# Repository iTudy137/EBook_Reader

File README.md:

### Copyright Dinca Tudor-Cristian 332CA 2025

# OpenBook E-Reader

1. [Block Diagram](#block-diagram)
2. [Bill of Materials](#bill-of-materials)
3. [Hardware Details](#hardware-functionality)
4. [ESP32-C6 Pins](#ESP32-C6-pin-mapping)

# Block Diagram

---

# Bill of Materials

| Qty | Description                                                                                                                                                                                                                                                                                                                                                                                                                                                                                          | Value                                                                          | Parts                                                                                                   | AVAILABILITY            | CHECK_PRICES                                                                                                                                                                                                                                                                                                                                                                                                                                                                                                                                                                                 | DATASHEET                                                                                                                                                |
| --- | ---------------------------------------------------------------------------------------------------------------------------------------------------------------------------------------------------------------------------------------------------------------------------------------------------------------------------------------------------------------------------------------------------------------------------------------------------------------------------------------------------- | ------------------------------------------------------------------------------ | ------------------------------------------------------------------------------------------------------- | ----------------------- | -------------------------------------------------------------------------------------------------------------------------------------------------------------------------------------------------------------------------------------------------------------------------------------------------------------------------------------------------------------------------------------------------------------------------------------------------------------------------------------------------------------------------------------------------------------------------------------------- | -------------------------------------------------------------------------------------------------------------------------------------------------------- |
| 1   | LED                                                                                                                                                                                                                                                                                                                                                                                                                                                                                                  |                                                                                | CHG_LED                                                                                                 | In Stock                | https://ro.mouser.com/ProductDetail/ams-OSRAM/LB-Q99G.01-P1R1-35-1?qs=IPgv5n7u5QZHWhEkNg3xgA%3D%3D                                                                                                                                                                                                                                                                                                                                                                                                                                                                                           | https://ro.mouser.com/datasheet/2/588/prd_pim_datasheet_23471863_EN_pdf-3317093.pdf                                                                      |
| 1   | SMD solder JUMPER                                                                                                                                                                                                                                                                                                                                                                                                                                                                                    |                                                                                | SJ1                                                                                                     | In Stock                | https://ro.mouser.com/ProductDetail/Vishay-Dale/CRCW04020000Z0EEHP?qs=sGAEpiMZZMtlubZbdhIBIKF%2FTFcY2hSpgvMg4uB1QYw%3D                                                                                                                                                                                                                                                                                                                                                                                                                                                                       | https://www.vishay.com/docs/20043/crcwhpe3.pdf                                                                                                           |
| 1   | CAPACITOR, European symbol                                                                                                                                                                                                                                                                                                                                                                                                                                                                           | 0.1uF/50V                                                                      | EPD_C5                                                                                                  | In Stock                | [https://ro.mouser.com/ProductDetail/Walsin/0402N151F500CT?qs=ZrPdAQfJ6DML0ptnM%2FXFsA%3D%3D&utm_id=6470900573&utm_source=google&utm_medium=cpc&utm_marketing_tactic=emeacorp&gad_source=1&gclid=Cj0KCQjwhr6_BhD4ARIsAH1YdjB1QLZVHFVJAtMd1vwkIhjE6qN7B49LVIzW80TzkBiTwUEhFkgf5tQaAoaREALw_wcB](https://ro.mouser.com/ProductDetail/Walsin/0402N151F500CT?qs=ZrPdAQfJ6DML0ptnM%2FXFsA%3D%3D&utm_id=6470900573&utm_source=google&utm_medium=cpc&utm_marketing_tactic=emeacorp&gad_source=1&gclid=Cj0KCQjwhr6_BhD4ARIsAH1YdjB1QLZVHFVJAtMd1vwkIhjE6qN7B49LVIzW80TzkBiTwUEhFkgf5tQaAoaREALw_wcB) | [https://ro.mouser.com/datasheet/2/210/WTC_MLCC_General_Purpose-1534899.pdf](https://ro.mouser.com/datasheet/2/210/WTC_MLCC_General_Purpose-1534899.pdf) |
| 1   | RESISTOR, European symbol                                                                                                                                                                                                                                                                                                                                                                                                                                                                            | 0.47                                                                           | R3                                                                                                      | In Stock                | https://ro.mouser.com/ProductDetail/Panasonic/ERJ-2BQJR47X?qs=18kBAoNi3c8r%252BkU3FsPM2Q%3D%3D                                                                                                                                                                                                                                                                                                                                                                                                                                                                                               | https://industrial.panasonic.com/cdbs/www-data/pdf/RDN0000/AOA0000C313.pdf                                                                               |
| 1   | RESISTOR, European symbol                                                                                                                                                                                                                                                                                                                                                                                                                                                                            | 100K                                                                           | R1_PWRUSB                                                                                               | In Stock                | [https://ro.mouser.com/ProductDetail/Welwyn-Components-TT-Electronics/WCR0402-100KFA?qs=%2F5Ar%2FAxv93DcWIrqMX6zjw%3D%3D](https://ro.mouser.com/ProductDetail/Welwyn-Components-TT-Electronics/WCR0402-100KFA?qs=%2F5Ar%2FAxv93DcWIrqMX6zjw%3D%3D)                                                                                                                                                                                                                                                                                                                                           | https://ro.mouser.com/datasheet/2/414/TTRB_S_A0012915158_1-2565570.pdf                                                                                   |
| 6   | CAPACITOR, European symbol                                                                                                                                                                                                                                                                                                                                                                                                                                                                           | 100nF                                                                          | C1, C2, C6, C8, C10, C_DELAY                                                                            | In Stock                | https://ro.mouser.com/ProductDetail/KYOCERA-AVX/04023C104KAT2A-62?qs=%252BdQmOuGyFcH%2FNuvX5KIF9Q%3D%3D                                                                                                                                                                                                                                                                                                                                                                                                                                                                                      | https://ro.mouser.com/datasheet/2/40/X7RDielectric-2943470.pdf                                                                                           |
| 2   | CAPACITOR, European symbol                                                                                                                                                                                                                                                                                                                                                                                                                                                                           | 100nF                                                                          | C4_USB, C9                                                                                              | In Stock                | https://ro.mouser.com/ProductDetail/KYOCERA-AVX/04023C104KAT2A-62?qs=%252BdQmOuGyFcH%2FNuvX5KIF9Q%3D%3D                                                                                                                                                                                                                                                                                                                                                                                                                                                                                      | https://ro.mouser.com/datasheet/2/40/X7RDielectric-2943470.pdf                                                                                           |
| 1   | POLARIZED CAPACITOR, European symbol                                                                                                                                                                                                                                                                                                                                                                                                                                                                 | 100uF TANT                                                                     | C3                                                                                                      | In Stock                | https://ro.mouser.com/ProductDetail/KYOCERA-AVX/TCJB106M020R0150E?qs=DPoM0jnrROXN%252B%252BcGKR%2FSYA%3D%3D&srsltid=AfmBOoo1FzSeu9BDfQsWfsf6aT2Nks-cpAUpOlGyrzjX172lod-o8mYB                                                                                                                                                                                                                                                                                                                                                                                                                 | https://ro.mouser.com/datasheet/2/40/TCJ-2887130.pdf                                                                                                     |
| 16  | RESISTOR, European symbol                                                                                                                                                                                                                                                                                                                                                                                                                                                                            | 10K                                                                            | R1, R1_PINH, R1_PINH1, R2-PINH, R2-PINH1, R4, R5, R6, R7, R8, R9, R10, R_BOOT, R_CHANGE, R_CL1, R_RESET | In Stock                | https://ro.mouser.com/ProductDetail/YAGEO/RC0402FR-07100KL?qs=mnq%2FyloZIXzTlUn7JAHSWg%3D%3D                                                                                                                                                                                                                                                                                                                                                                                                                                                                                                 | https://ro.mouser.com/datasheet/2/447/YAGEO_PYu_RC_Group_51_RoHS_L_12-3313492.pdf                                                                        |
| 1   | CAPACITOR, European symbol                                                                                                                                                                                                                                                                                                                                                                                                                                                                           | 10uF                                                                           | C7                                                                                                      | In Stock                | https://ro.mouser.com/ProductDetail/KYOCERA-AVX/KAM05AR71E103KH?qs=Jm2GQyTW%2FbgMbf7pmhTrvw%3D%3D                                                                                                                                                                                                                                                                                                                                                                                                                                                                                            | https://ro.mouser.com/datasheet/2/40/AutoMLCCKAM-3216307.pdf                                                                                             |
| 1   | Micro SD Card Socket, Push-Push Type, Top Mount, SMT, H=1.83mm, 10u                                                                                                                                                                                                                                                                                                                                                                                                                                  | 112A-TAAR-R03_ATTEND                                                           | J4                                                                                                      | In Stock                | https://www.soselectronic.com/ro-ro/products/attend/112a-taar-r03-116052                                                                                                                                                                                                                                                                                                                                                                                                                                                                                                                     | https://cdn.soselectronic.com/productdata/bd/ac/42954337/112a-taar-r03.pdf                                                                               |
| 1   | RESISTOR, European symbol                                                                                                                                                                                                                                                                                                                                                                                                                                                                            | 15                                                                             | R_CAPACITOR                                                                                             | In Stock                | https://ro.mouser.com/ProductDetail/Bourns/CR0402-FX-15R0GLF?qs=sGAEpiMZZMtlubZbdhIBICGkyIRIR3aIuucn1Gj71Hk%3D                                                                                                                                                                                                                                                                                                                                                                                                                                                                               | https://ro.mouser.com/datasheet/2/54/cr-1858361.pdf                                                                                                      |
| 1   | CAPACITOR, European symbol                                                                                                                                                                                                                                                                                                                                                                                                                                                                           | 1uF                                                                            | C5                                                                                                      | In Stock                | https://ro.mouser.com/ProductDetail/TAIYO-YUDEN/MAASL105CC7105MFCA01?qs=HFfMDpzxxd1Fn%2FInbJA7vw%3D%3D                                                                                                                                                                                                                                                                                                                                                                                                                                                                                       | https://ro.mouser.com/datasheet/2/396/TAIYO_YUDEN_04_27_2024_c_mlcc_A_e1-3451516.pdf                                                                     |
| 9   | CAPACITOR, European symbol                                                                                                                                                                                                                                                                                                                                                                                                                                                                           | 1uF/50V                                                                        | EPD_C1, EPD_C2, EPD_C6, EPD_C7, EPD_C8, EPD_C9, EPD_C10, EPD_C11, EPD_C12                               | In Stock                | https://ro.mouser.com/ProductDetail/TAIYO-YUDEN/MAASU32NSB7105KTCA01?qs=sGAEpiMZZMukHu%252BjC5l7YTv8iICJ6%2Fau7q9mUPeDLKU%3D                                                                                                                                                                                                                                                                                                                                                                                                                                                                 | https://ro.mouser.com/datasheet/2/396/TDK_4_24_2024_MAASU32NSB7105KTCA01_SS-3440852.pdf                                                                  |
| 1   | RESISTOR, European symbol                                                                                                                                                                                                                                                                                                                                                                                                                                                                            | 2.2                                                                            | R2                                                                                                      | In Stock                | https://ro.mouser.com/ProductDetail/YAGEO/RC0402JR-072R2L?qs=sGAEpiMZZMtlubZbdhIBIDHZZHtX2mqkbiSU5pja5tk%3D                                                                                                                                                                                                                                                                                                                                                                                                                                                                                  | https://ro.mouser.com/datasheet/2/447/YAGEO_PYu_RC_Group_51_RoHS_L_12-3313492.pdf                                                                        |
| 1   | RESISTOR, European symbol                                                                                                                                                                                                                                                                                                                                                                                                                                                                            | 200                                                                            | R1_BAT                                                                                                  | In Stock                | https://ro.mouser.com/ProductDetail/Panasonic/ERJ-U02D2000X?qs=sGAEpiMZZMtlubZbdhIBICc%2FOdEF9c%2FXmWyuMKnNE4Y%3D                                                                                                                                                                                                                                                                                                                                                                                                                                                                            | https://industrial.panasonic.com/cdbs/www-data/pdf/RDP0000/AOA0000C334.pdf                                                                               |
| 2   | P-channel MOSFETs                                                                                                                                                                                                                                                                                                                                                                                                                                                                                    | 20V/4.2A/52mO/1.4W                                                             | Q1, Q2                                                                                                  | In Stock                | https://ro.mouser.com/ProductDetail/Diodes-Incorporated/DMG2305UX-7?qs=L1DZKBg7t5F%2FNBHrjfxC%252Bg%3D%3D&utm_id=6470900573&utm_source=google&utm_medium=cpc&utm_marketing_tactic=emeacorp&gad_source=1&gclid=Cj0KCQjwhr6_BhD4ARIsAH1YdjDoeyMOZmPtNXLmjl3ngvDMqv7Q8ZoL57iNF_dxsnN5I3NCajG9PIEaAkOEEALw_wcB                                                                                                                                                                                                                                                                                   | https://www.diodes.com/assets/Datasheets/DMG2305UX.pdf                                                                                                   |
| 1   | RESISTOR, European symbol                                                                                                                                                                                                                                                                                                                                                                                                                                                                            | 2K                                                                             | R2_BAT                                                                                                  | In Stock                | https://ro.mouser.com/ProductDetail/Vishay-Dale/CRCW04022K00JNTD?qs=D1%252BtGGlbRE%252BwoJgrHBlX1g%3D%3D                                                                                                                                                                                                                                                                                                                                                                                                                                                                                     | https://www.vishay.com/docs/20008/dcrcw.pdf                                                                                                              |
| 2   | CAPACITOR, European symbol                                                                                                                                                                                                                                                                                                                                                                                                                                                                           | 4.7uF                                                                          | C1_BAT, C2_BAT                                                                                          | In Stock                | https://ro.mouser.com/ProductDetail/KEMET/C0402C475K8PACTU?qs=ulEaXIWI0c9ebKRT3r3htg%3D%3D                                                                                                                                                                                                                                                                                                                                                                                                                                                                                                   | https://ro.mouser.com/datasheet/2/447/KEM_C1006_X5R_SMD-3316465.pdf                                                                                      |
| 3   | CAPACITOR, European symbol                                                                                                                                                                                                                                                                                                                                                                                                                                                                           | 4.7uF                                                                          | C1_BAT1, C1_BAT2, C5_USB                                                                                | In Stock                | https://ro.mouser.com/ProductDetail/KEMET/C0402C475K8PACTU?qs=ulEaXIWI0c9ebKRT3r3htg%3D%3D                                                                                                                                                                                                                                                                                                                                                                                                                                                                                                   | https://ro.mouser.com/datasheet/2/447/KEM_C1006_X5R_SMD-3316465.pdf                                                                                      |
| 1   | CAPACITOR, European symbol                                                                                                                                                                                                                                                                                                                                                                                                                                                                           | 4.7uF/25V                                                                      | C4                                                                                                      | In Stock                | https://ro.mouser.com/ProductDetail/KYOCERA-AVX/CM05X5R475M25AH?qs=MyNHzdoqoQJvFdZaEuclBg%3D%3D                                                                                                                                                                                                                                                                                                                                                                                                                                                                                              | https://ro.mouser.com/datasheet/2/40/CM_Series_e-2835982.pdf                                                                                             |
| 2   | RESISTOR, European symbol                                                                                                                                                                                                                                                                                                                                                                                                                                                                            | 5k1                                                                            | R2-USB, R2-USB1                                                                                         | In Stock                | https://ro.mouser.com/ProductDetail/Vishay-Beyschlag/MCS04020C5101FE000?qs=sGAEpiMZZMvdGkrng054t4QdAY%2FQ0LweI%252Blr2dxb1tw%3D                                                                                                                                                                                                                                                                                                                                                                                                                                                              | https://www.vishay.com/docs/28705/mcx0x0xpro.pdf                                                                                                         |
| 1   |                                                                                                                                                                                                                                                                                                                                                                                                                                                                                                      | 68uH                                                                           | L1                                                                                                      | In Stock                | https://www.digikey.de/en/products/detail/w%C3%BCrth-elektronik/744043680/1638515?srsltid=AfmBOopBgKiLEiasm_81lCn1a11PPzCKGdFMi1JqFSJ8kTFummtD-o78                                                                                                                                                                                                                                                                                                                                                                                                                                           | https://www.we-online.com/components/products/datasheet/744043680.pdf                                                                                    |
| 1   | Voltage Detector with Adjustable Delay Time: CMOS processes are utilized to develop high precision, low current consumption CMOS reset ICs that allow arbitrary setting of the delay time. The extensive lineup includes both Nch Open Drain and CMOS output types in a wide range of detection voltages (from 2.3V to 6.0V, in 0.1V steps), enabling selection of the ideal solution based on customer requirements. In addition, the entire series is of course both lead-free and RoHS-compliant. | BD5229G-TR                                                                     | IC1                                                                                                     | In Stock                | https://ro.mouser.com/ProductDetail/ROHM-Semiconductor/BD5229G-1TR?qs=HoCaDK9Nz5dKF71NR7zdNw%3D%3D&utm_id=6470900573&utm_source=google&utm_medium=cpc&utm_marketing_tactic=emeacorp&gad_source=1&gclid=Cj0KCQjwhr6_BhD4ARIsAH1YdjAIpE6_2POwpfdw6DR7vakM2s_-m0lDV7xt7KL-rvPk8BHaBd_4NeAaAozdEALw_wcB                                                                                                                                                                                                                                                                                          | https://fscdn.rohm.com/en/products/databook/datasheet/ic/power/voltage_detector/bd52xxg-1-e.pdf                                                          |
| 3   |                                                                                                                                                                                                                                                                                                                                                                                                                                                                                                      | BUTTON_CUSYOMV1                                                                | BOOT_BUTTON, CHANGE_BUTTON, RESET_BUTTON                                                                | Restricted Availability | https://ro.mouser.com/ProductDetail/Panasonic/EVQ-P7B01K?qs=Ow%252BOiPmaljGz0yYR%252BWV0ZQ%3D%3D                                                                                                                                                                                                                                                                                                                                                                                                                                                                                             | https://industry.panasonic.com/global/en/downloads/?file_cd=402906&tab=catalog&series_cd=3457                                                            |
| 1   | Cap 0.011F 3.3V 1210 Flat Check availability                                                                                                                                                                                                                                                                                                                                                                                                                                                         | CPH3225A                                                                       | C10_SUPERCAP                                                                                            | Not in stock            | [https://www.snapeda.com/parts/CPH3225A/Seiko+Instruments/view-part/?ref=eda](https://www.snapeda.com/parts/CPH3225A/Seiko+Instruments/view-part/?ref=eda)                                                                                                                                                                                                                                                                                                                                                                                                                                   | https://www.snapeda.com/parts/CPH3225A/Seiko%20Instruments/datasheet/                                                                                    |
| 1   | Real Time Clock Serial 16-Pin SOIC W T/R     Check availability                                                                                                                                                                                                                                                                                                                                                                                                                                      | DS3231SN#                                                                      | U3                                                                                                      | In Stock                | [https://www.snapeda.com/parts/DS3231SN%23/Analog+Devices/view-part/?ref=eda](https://www.snapeda.com/parts/DS3231SN%23/Analog+Devices/view-part/?ref=eda)                                                                                                                                                                                                                                                                                                                                                                                                                                   | https://www.snapeda.com/parts/DS3231SN%23/Analog%20Devices/datasheet/                                                                                    |
| 1   | Check availability                                                                                                                                                                                                                                                                                                                                                                                                                                                                                   | ESP32-C6-WROOM-1-N8                                                            | U2                                                                                                      | In Stock                | [https://www.snapeda.com/parts/ESP32-C6-WROOM-1-N8/Espressif+Systems/view-part/?ref=eda](https://www.snapeda.com/parts/ESP32-C6-WROOM-1-N8/Espressif+Systems/view-part/?ref=eda)                                                                                                                                                                                                                                                                                                                                                                                                             | https://www.snapeda.com/parts/ESP32-C6-WROOM-1-N8/Espressif%20Systems/datasheet/                                                                         |
| 1   | VARISTOR                                                                                                                                                                                                                                                                                                                                                                                                                                                                                             | ESP32C6_VARISTORCN1812                                                         | PFMF.050.1                                                                                              | In Stock                | https://ro.mouser.com/ProductDetail/Schurter/PFMF.050.2?qs=1auRipcfynCums5v1iucSA%3D%3D                                                                                                                                                                                                                                                                                                                                                                                                                                                                                                      | https://ro.mouser.com/datasheet/2/358/typ_PFMF-1275918.pdf                                                                                               |
| 2   | Schottky Barrier Rectifier Diode                                                                                                                                                                                                                                                                                                                                                                                                                                                                     | ESP32_WROVER_AVX---SD0805S020S1R0_AVX_SD0805S020S1R0_0_0AVX_SD0805S020S1R0_0_0 | D2, D7                                                                                                  | In Stock                | https://ro.mouser.com/ProductDetail/KYOCERA-AVX/SD0805S020S1R0?qs=jCA%252BPfw4LHbpkAoSnwrdjw%3D%3D                                                                                                                                                                                                                                                                                                                                                                                                                                                                                           | [http://datasheets.avx.com/schottky.pdf](http://datasheets.avx.com/schottky.pdf)                                                                         |
| 1   | Integrated Environmental Unit                                                                                                                                                                                                                                                                                                                                                                                                                                                                        | ESP32_WROVER_BME680_BME680                                                     | SENSOR2                                                                                                 | In Stock                | https://ro.mouser.com/ProductDetail/Bosch-Sensortec/BME680?qs=v271MhAjFHjo0yA%2FC4OnDQ%3D%3D                                                                                                                                                                                                                                                                                                                                                                                                                                                                                                 | [https://ro.mouser.com/datasheet/2/783/BST_BME680_DS001-1509608.pdf](https://ro.mouser.com/datasheet/2/783/BST_BME680_DS001-1509608.pdf)                 |
| 1   | MCP73831T Li-Ion, Li-Pol Controller                                                                                                                                                                                                                                                                                                                                                                                                                                                                  | ESP32_WROVER_SPARKFUN-IC-POWER_MCP73831                                        | MCP73831                                                                                                | In Stock                | https://ro.mouser.com/ProductDetail/Microchip-Technology/MCP73831T-2DCI-OT?qs=yUQqVecv4qu38ml9qkvsJw%3D%3D                                                                                                                                                                                                                                                                                                                                                                                                                                                                                   | https://ro.mouser.com/datasheet/2/268/MCP73831_Family_Data_Sheet_DS20001984H-3441711.pdf                                                                 |
| 1   |  (0.50mm) Surface Mount, Right Angle                                                                                                                                                                                                                                                                                                                                                                                                                                                                 | FH34SRJ-24S-0.5SH_99_                                                          | J1                                                                                                      | In Stock                | https://ro.mouser.com/ProductDetail/Hirose-Connector/FH34SRJ-24S-0.5SH99?qs=vcbW%252B4%252BSTIpKBl5ap9J8Fw%3D%3D                                                                                                                                                                                                                                                                                                                                                                                                                                                                             | https://ro.mouser.com/datasheet/2/185/FH34SRJ_24S_0_5SH_99__CL0580_1255_6_99_2DDrawing_0-1615044.pdf                                                     |
| 1   | Check availability                                                                                                                                                                                                                                                                                                                                                                                                                                                                                   | MAX17048G+T10                                                                  | U4                                                                                                      | In Stock                | [https://www.snapeda.com/parts/MAX17048G+T10/Analog+Devices/view-part/?ref=eda](https://www.snapeda.com/parts/MAX17048G+T10/Analog+Devices/view-part/?ref=eda)                                                                                                                                                                                                                                                                                                                                                                                                                               | https://www.snapeda.com/parts/MAX17048G+T10/Analog%20Devices/datasheet/                                                                                  |
| 3   | ON SEMICONDUCTOR - MBR0530 - DIODE, SCHOTTKY, 0.5A, 30V, SOD-123                                                                                                                                                                                                                                                                                                                                                                                                                                     | MBR0530                                                                        | D3, D4, D5                                                                                              | In Stock                | [https://www.snapeda.com/parts/MBR0530/Onsemi/view-part/?ref=eda](https://www.snapeda.com/parts/MBR0530/Onsemi/view-part/?ref=eda)                                                                                                                                                                                                                                                                                                                                                                                                                                                           | https://www.snapeda.com/parts/MBR0530/ON%20Semiconductor/datasheet/                                                                                      |
| 6   | Check availability                                                                                                                                                                                                                                                                                                                                                                                                                                                                                   | PGB1010603MR                                                                   | D6, D8, D9, D10, D11, D12                                                                               | In Stock                | [https://www.snapeda.com/parts/PGB1010603MR/Littelfuse/view-part/?ref=eda](https://www.snapeda.com/parts/PGB1010603MR/Littelfuse/view-part/?ref=eda)                                                                                                                                                                                                                                                                                                                                                                                                                                         | https://www.snapeda.com/parts/PGB1010603MR/Littelfuse%20Inc./datasheet/                                                                                  |
| 1   | SparkFun I2C Standard Qwiic Connector                                                                                                                                                                                                                                                                                                                                                                                                                                                                | QWIIC_RIGHT_ANGLE                                                              | J3                                                                                                      | In Stock                | https://ro.mouser.com/ProductDetail/SparkFun/PRT-14417?qs=wd5RIQLrsJhgdz%2FpmZ%2F3GQ%3D%3D                                                                                                                                                                                                                                                                                                                                                                                                                                                                                                   | https://ro.mouser.com/datasheet/2/813/Qwiic_Connector_Datasheet-1223982.pdf                                                                              |
| 1   | CONN USB 2.0 TYPE-C R/A SMT                                                                                                                                                                                                                                                                                                                                                                                                                                                                          | SAMACSYS_PARTS_USB4110-GF-A                                                    | J2                                                                                                      | In Stock                | https://ro.mouser.com/ProductDetail/GCT/USB4110-GF-A?qs=KUoIvG%2F9IlYiZvIXQjyJeA%3D%3D                                                                                                                                                                                                                                                                                                                                                                                                                                                                                                       | https://ro.mouser.com/datasheet/2/837/GCT_USB4110_Product_Drawing___20k_cycles-3455479.pdf                                                               |
| 1   | MOSFET N-Ch 30V 1.5A TrenchFET SC70 Vishay Si1308EDL-T1-GE3 N-channel MOSFET Transistor, 1.5 A, 30 V, 3-Pin SC-70                                                                                                                                                                                                                                                                                                                                                                                    | SI1308EDL-T1-GE3                                                               | Q3                                                                                                      | In Stock                | [https://www.snapeda.com/parts/SI1308EDL-T1-GE3/Vishay+Siliconix/view-part/?ref=eda](https://www.snapeda.com/parts/SI1308EDL-T1-GE3/Vishay+Siliconix/view-part/?ref=eda)                                                                                                                                                                                                                                                                                                                                                                                                                     | https://www.snapeda.com/parts/SI1308EDL-T1-GE3/Vishay%20Siliconix/datasheet/                                                                             |
| 17  | Test pad                                                                                                                                                                                                                                                                                                                                                                                                                                                                                             | TPTP20R                                                                        | TP1, TP2, TP3, TP4, TP5, TP6, TP7, TP8, TP9, TP10, TP11, TP12, TP13, TP14, TP15, TP16, TP17             |                         | Custom                                                                                                                                                                                                                                                                                                                                                                                                                                                                                                                                                                                       | Custom                                                                                                                                                   |
| 1   | Low Cap. ESD Protection Auto SOT-23-6 STMicroelectronics USBLC6-2SC6Y, Dual Uni-Directional TVS Diode Array, 6-Pin SOT-23                                                                                                                                                                                                                                                                                                                                                                            | USBLC6-2SC6Y                                                                   | D1                                                                                                      | In Stock                | [https://www.snapeda.com/parts/USBLC6-2SC6Y/STMicroelectronics/view-part/?ref=eda](https://www.snapeda.com/parts/USBLC6-2SC6Y/STMicroelectronics/view-part/?ref=eda)                                                                                                                                                                                                                                                                                                                                                                                                                         | https://www.snapeda.com/parts/USBLC6-2SC6Y/STMicroelectronics/datasheet/                                                                                 |
| 1   | Check availability                                                                                                                                                                                                                                                                                                                                                                                                                                                                                   | W25Q512JVEIQ                                                                   | U1                                                                                                      | In Stock                | [https://www.snapeda.com/parts/W25Q512JVEIQ/Winbond+Electronics/view-part/?ref=eda](https://www.snapeda.com/parts/W25Q512JVEIQ/Winbond+Electronics/view-part/?ref=eda)                                                                                                                                                                                                                                                                                                                                                                                                                       | https://www.snapeda.com/parts/W25Q512JVEIQ/Winbond%20Electronics/datasheet/                                                                              |
| 1   | LDO Voltage Regulators                                                                                                                                                                                                                                                                                                                                                                                                                                                                               | XC6220A331MR-G                                                                 | IC4                                                                                                     | In Stock                | https://ro.mouser.com/ProductDetail/Torex-Semiconductor/XC6220A331MR-G?qs=AsjdqWjXhJ8ZSWznL1J0gg%3D%3D                                                                                                                                                                                                                                                                                                                                                                                                                                                                                       | https://ro.mouser.com/datasheet/2/760/xc6220-3371556.pdf                                                                                                 |

---

# Hardware Functionality

### Microcontroller - ESP32-C6
- **Interfaces:** SPI, I2C, GPIO, USB, PWM
- **Functions:** Wi-Fi/BLE communication, display control, sensor reading, user interface, power management
- **Operating Voltage:** 3.3V

### 1. E-Paper Display (Waveshare WSH-13187 7.5" / SPI)
- **Resolution:** 800x480
- **Interface:** SPI + GPIO  
  - **CS, DC, RST, BUSY**
- **Connected via dedicated header**

### 2. BME688 Sensor (Bosch)
- **Measures:** temperature, pressure, humidity, air quality
- **Interface:** I2C
- **Address:** configurable (default 0x76)
- **Operating Voltage:** 3.3V

### 3. RTC - DS3231SN
- **Function:** Real-Time Clock with supercapacitor backup
- **Interface:** I2C
- **Backup:** 1F Supercapacitor
- **Accuracy:** ±2ppm

### 4. Power Supply
- **Battery:** 2500mAh Li-Po
- **Charging IC:** MCP73831 (linear charger, 3.7V battery)
- **LDO Regulator:** 3.3V (AMS1117 or equivalent)
- **Connector:** USB-C (with ESD protection)

### 5. Battery Management
- **Fuel Gauge:** MAX17048
- **I2C, enables battery level monitoring**

### 6. SD Card
- **Interface:** SPI
- **Usage:** e-book storage

### 7. User Interface
- **RESET Button**
- **3 Input Buttons connected to GPIO + RC debouncing**
- **Functions:** menu navigation, page switching, simple interactions

### 8. Qwiic / Stemma QT Connector
- **Allows easy expansion with external I2C sensors**

---

## 🔋 Battery & Power Usage Summary

### 📦 Battery Capacity
- **2500mAh @ 3.7V = 9.25Wh**

---

### ⚡ Power Consumption Overview

| Mode                | Current Draw | Power (W) | Battery Life       |
|---------------------|--------------|-----------|---------------------|
| 🔘 Idle (Deep Sleep) | ~0.05 mA     | ~0.0002 W | ~5.7 years          |
| 😴 Light Sleep       | ~1.2 mA      | ~0.0044 W | ~86 days            |
| 📖 Active Reading    | ~77 mA       | ~0.285 W  | ~32 hours           |
| 🌐 Wi-Fi Active      | ~177 mA      | ~0.655 W  | ~14 hours           |

---

# ESP32-C6 Pin Mapping

| **ESP32-C6 Pin** | **Net Label**  | **Function**       | **Connected Component**      | **Purpose / Description**                                                                 |
|------------------|----------------|--------------------|-------------------------------|-------------------------------------------------------------------------------------------|
| EN               | RESET          | Enable             | ESP32-C6                      | Main reset input to the microcontroller                                                   |
| IO0              | INT_RTC        | GPIO (Interrupt)   | RTC DS3231SN                  | Receives interrupt signal from RTC (e.g. alarm trigger)                                  |
| IO1              | 32KHZ          | GPIO (Clock In)    | RTC DS3231SN                  | 32kHz clock output from RTC                                                               |
| IO2              | MISO           | SPI MISO           | SD Card                       | Receives data from SD card                                                                |
| IO3              | EPD_BUSY       | GPIO (Input)       | E-Paper Display               | Indicates when the E-Paper display is busy                                               |
| IO4              | SS_SD          | SPI CS             | SD Card                       | Chip select for SD card                                                                   |
| IO5              | EPD_CS         | SPI CS             | E-Paper Display               | Chip select for E-Paper display                                                           |
| IO6              | SCK            | SPI Clock          | E-Paper Display, SD Card      | Clock signal for shared SPI bus                                                           |
| IO7              | MOSI           | SPI MOSI           | E-Paper Display, SD Card      | Sends data to display and SD card                                                         |
| IO8              | GPIO9          | GPIO               | General Purpose               | Spare GPIO or future expansion                                                            |
| IO9              | IO/BOOT        | GPIO / Boot        | Boot Button                   | Used for flashing the ESP32 (held LOW on boot to enter flash mode)                       |
| IO10             | EPD_CS         | SPI CS             | E-Paper Display               | Redundant label for CS (appears twice in schematic)                                       |
| IO11             | FLASH_CS       | SPI CS             | External NOR Flash            | Chip select for SPI flash                                                                 |
| IO12             | USB_D-         | USB D-             | USB-C Connector               | Native USB communication                                                                 |
| IO13             | USB_D+         | USB D+             | USB-C Connector               | Native USB communication                                                                 |
| IO15             | IO/CHANGE      | GPIO               | General Purpose / Input       | Connected to a user-defined I/O (possibly an interrupt line or button)                   |
| IO16             | TX             | UART TX            | Serial Communication          | Transmit line for UART debugging                                                          |
| IO17             | RX             | UART RX            | Serial Communication          | Receive line for UART debugging                                                           |
| IO18             | RTC_RST        | GPIO               | RTC DS3231SN                  | Allows resetting the RTC externally                                                       |
| IO19             | I2C_PW         | GPIO (Power Ctrl)  | I2C Peripherals               | Enables power to I2C devices (BME688, MAX17048, etc.)                                     |
| IO20             | EPD_3V3_C      | GPIO (Power Ctrl)  | E-Paper Display               | Powers the EPD circuit via transistor / switch                                            |
| IO21             | SDA            | I2C Data           | BME688, RTC, MAX17048         | Shared data line for I2C peripherals                                                      |
| IO22             | SCL            | I2C Clock          | BME688, RTC, MAX17048         | Shared clock line for I2C peripherals                                                     |
| IO23             | EPD_RSR        | GPIO               | E-Paper Display               | Reset line for E-Paper display                                                            |
| 3V3              | 3V3            | Power              | All Components                | Main power rail (3.3V)                                                                    |
| GND              | GND            | Ground             | All Components                | Ground reference for the entire system                                                    |

---

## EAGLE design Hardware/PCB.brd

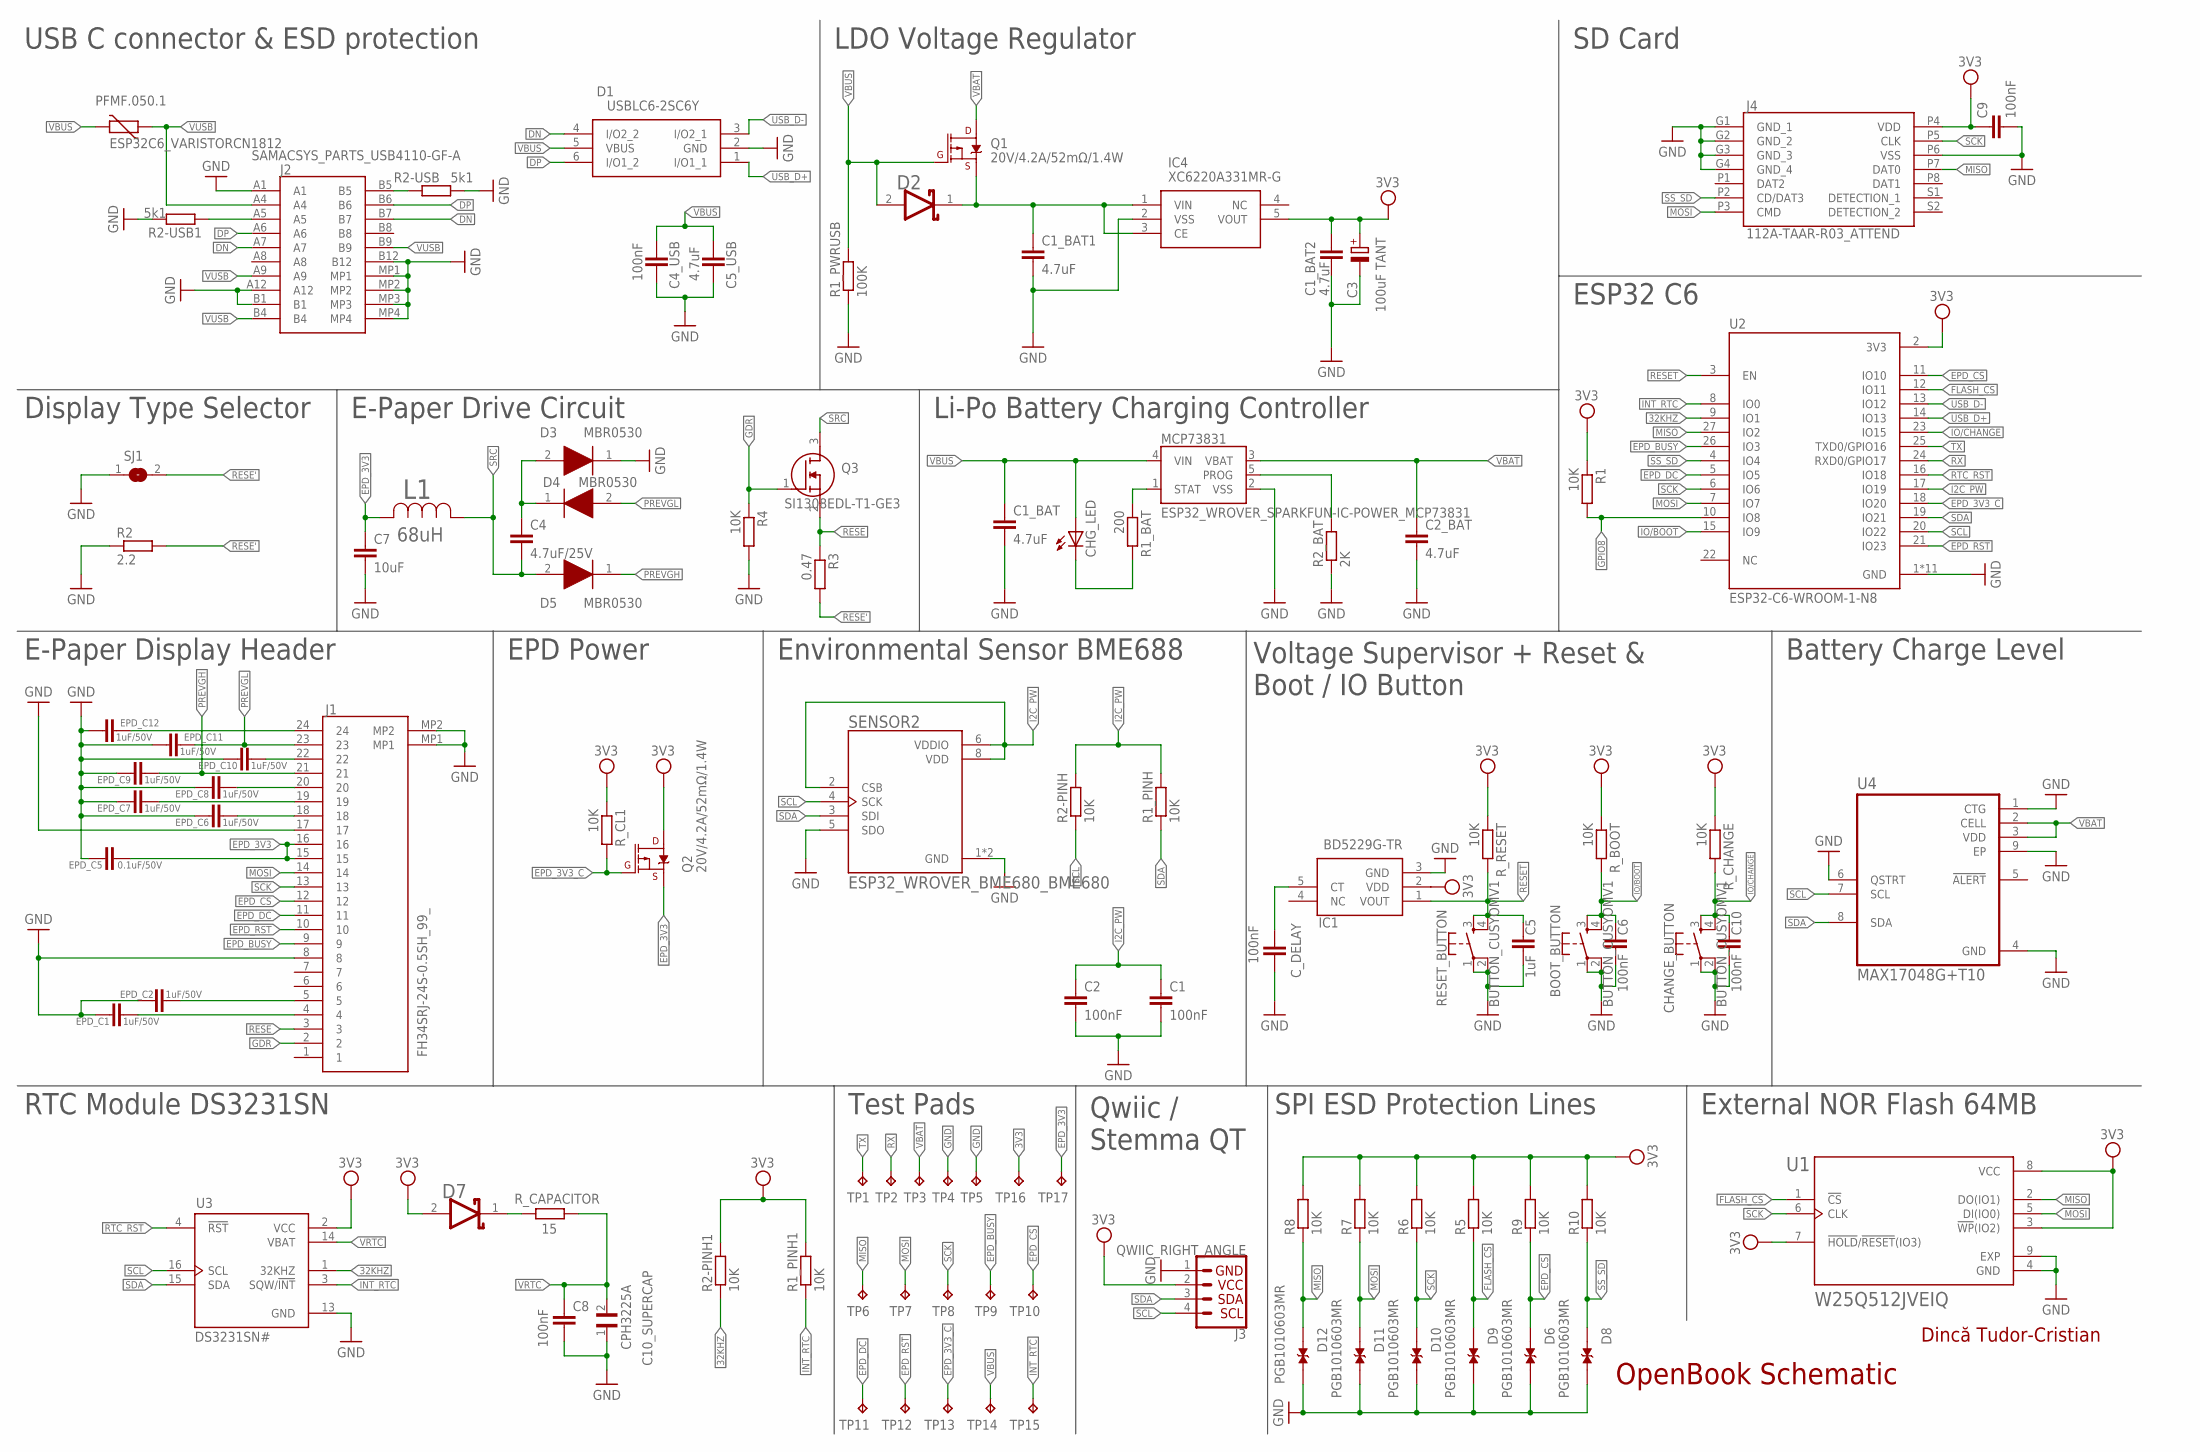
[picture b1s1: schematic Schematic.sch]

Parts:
BOOT_BUTTON: BUTTON_CUSYOMV1; MYBUTTON
C1, C2, C4_USB, C6, C8, C9, C10: 100nF; EAGLE-LTSPICE_C0402
C1_BAT, C1_BAT1, C1_BAT2, C2_BAT, C5_USB: 4.7uF; EAGLE-LTSPICE_C0402
C3: 100uF TANT; RCL_CT3528
C4: 4.7uF/25V; EAGLE-LTSPICE_C0402
C5: 1uF; EAGLE-LTSPICE_C0402
C7: 10uF; EAGLE-LTSPICE_C0402
C10_SUPERCAP: CPH3225A; CAPCP3225X100N
CHANGE_BUTTON: BUTTON_CUSYOMV1; MYBUTTON
CHG_LED: ADAFRUIT_LEDCHIP-LED0603; ADAFRUIT_CHIP-LED0603
C_DELAY: 100nF; EAGLE-LTSPICE_C0402
D1: USBLC6-2SC6Y; SOT95P280X145-6N
D2, D7: ESP32_WROVER_AVX---SD0805S020S1R0_AVX_SD0805S020S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; ESP32_WROVER_AVX---SD0805S020S1R0_AVX_SD0805S020S1R0_0
D3, D4, D5: MBR0530; SOD3716X135N
D6, D8, D9, D10, D11, D12: PGB1010603MR; DIOC1608X36N
EPD_C1, EPD_C2, EPD_C6, EPD_C7, EPD_C8, EPD_C9, EPD_C10, EPD_C11, EPD_C12: 1uF/50V; EAGLE-LTSPICE_C0402
EPD_C5: 0.1uF/50V; EAGLE-LTSPICE_C0402
IC1: BD5229G-TR; SOT95P280X125-5N
IC4: XC6220A331MR-G; SOT95P280X120-5N
J1: FH34SRJ-24S-0.5SH_99_; FH34SRJ24S05SH99
J2: SAMACSYS_PARTS_USB4110-GF-A; SAMACSYS_PARTS_USB4110GFA
J3: QWIIC_RIGHT_ANGLE; JST04_1MM_RA
J4: 112A-TAAR-R03_ATTEND; 112ATAARR03ATTEND
L1: 68uH; IND_4828-WE-TPC_WRE
MCP73831: ESP32_WROVER_SPARKFUN-IC-POWER_MCP73831; ESP32_WROVER_SPARKFUN-IC-POWER_SOT23-5
PFMF.050.1: ESP32C6_VARISTORCN1812; ESP32C6_VARISTOR_CT/CN1812
Q1, Q2: 20V/4.2A/52mΩ/1.4W; ESP32_WROVER_SPARKFUN-DISCRETESEMI_SOT23-3
Q3: SI1308EDL-T1-GE3; SOT65P210X110-3N
R1, R1_PINH, R1_PINH1, R2-PINH, R2-PINH1, R4, R5, R6, R7, R8, R9, R10: 10K; ESP32_WROVER_EAGLE-LTSPICE_R0402
R1_BAT: 200; ESP32_WROVER_EAGLE-LTSPICE_R0402
R1_PWRUSB: 100K; ESP32_WROVER_EAGLE-LTSPICE_R0402
R2: 2.2; ESP32_WROVER_EAGLE-LTSPICE_R0402
R2-USB, R2-USB1: 5k1; ESP32_WROVER_EAGLE-LTSPICE_R0402
R2_BAT: 2K; ESP32_WROVER_EAGLE-LTSPICE_R0402
R3: 0.47; ESP32_WROVER_EAGLE-LTSPICE_R0402
RESET_BUTTON: BUTTON_CUSYOMV1; MYBUTTON
R_BOOT: 10K; ESP32_WROVER_EAGLE-LTSPICE_R0402
R_CAPACITOR: 15; ESP32_WROVER_EAGLE-LTSPICE_R0402
R_CHANGE: 10K; ESP32_WROVER_EAGLE-LTSPICE_R0402
R_CL1: 10K; ESP32_WROVER_EAGLE-LTSPICE_R0402
R_RESET: 10K; ESP32_WROVER_EAGLE-LTSPICE_R0402
SENSOR2: ESP32_WROVER_BME680_BME680; ESP32_WROVER_BME680_PSON80P300X300X100-8N
SJ1: SJ
TP1, TP2, TP3, TP4, TP5, TP6, TP7, TP8, TP9, TP10, TP11, TP12, TP13, TP14, TP15, TP16, TP17: TPTP20R; TP20R
U1: W25Q512JVEIQ; SON127P600X800X80-9N
U2: ESP32-C6-WROOM-1-N8; XCVR_ESP32-C6-WROOM-1-N8
U3: DS3231SN#; SOIC127P1032X265-16N
U4: MAX17048G+T10; SON50P200X200X80-9N

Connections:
3V3: C1_BAT2.1, C3.+, C9.1, D7.2 (ANODE), IC1.2 (VDD), IC4.5 (VOUT), J3.2, J4.P4 (VDD), Q2.3 (D), R1.1, R1_PINH1.2, R2-PINH1.2, R5.2, R6.2, R7.2, R8.2, R9.2, R10.2, R_BOOT.1, R_CHANGE.1, R_CL1.1, R_RESET.1, TP16.TP, U1.3 (!WP!(IO2)), U1.7 (!HOLD!/!RESET!(IO3)), U1.8 (VCC), U2.2 (3V3), U3.2 (VCC)
32KHZ: R2-PINH1.1, U2.9 (IO1), U3.1 (32KHZ)
DN: D1.4 (I/O2_2), J2.A7, J2.B7
DP: D1.6 (I/O1_2), J2.A6, J2.B6
EPD_3V3: C7.1, EPD_C5.1, J1.15, J1.16, L1.2, Q2.2 (S), TP17.TP
EPD_3V3_C: Q2.1 (G), R_CL1.2, TP13.TP, U2.18 (IO20)
EPD_BUSY: J1.9, TP9.TP, U2.26 (IO3)
EPD_CS: D6.1, J1.12, R9.1, TP10.TP, U2.11 (IO10)
EPD_DC: J1.11, TP11.TP, U2.5 (IO5)
EPD_RST: J1.10, TP12.TP, U2.21 (IO23)
FLASH_CS: D9.1, R5.1, U1.1 (!CS), U2.12 (IO11)
GDR: J1.2, Q3.1 (G), R4.1
GND: BOOT_BUTTON.1, BOOT_BUTTON.2, C1.2, C1_BAT.2, C1_BAT1.2, C1_BAT2.2, C2.2, C2_BAT.2, C3.-, C4_USB.2, C5.2, C5_USB.2, C6.2, C7.2, C8.2, C9.2, C10.2, C10_SUPERCAP.1, CHANGE_BUTTON.1, CHANGE_BUTTON.2, C_DELAY.2, D1.2 (GND), D3.1 (K), D6.2, D8.2, D9.2, D10.2, D11.2, D12.2, EPD_C1.2, EPD_C2.2, EPD_C5.2, EPD_C6.2, EPD_C7.2, EPD_C8.2, EPD_C9.2, EPD_C10.2, EPD_C11.2, EPD_C12.2, IC1.3 (GND), IC4.2 (VSS), J1.8, J1.17, J1.MP1, J1.MP2, J2.A1, J2.A12, J2.B1, J2.B12, J2.MP1, J2.MP2, J2.MP3, J2.MP4, J3.1, J4.G1 (GND_1), J4.G2 (GND_2), J4.G3 (GND_3), J4.G4 (GND_4), J4.P6 (VSS), MCP73831.2 (VSS), R1_PWRUSB.1, R2.1, R2-USB.2, R2-USB1.2, R2_BAT.1, R4.2, RESET_BUTTON.1, RESET_BUTTON.2, SENSOR2.1 (GND), SENSOR2.5 (SDO), SENSOR2.7 (GND), SJ1.1, TP4.TP, TP5.TP, U1.4 (GND), U1.9 (EXP), U2.1 (GND), U2.28 (GND), U2.29_1 (GND), U2.29_2 (GND), U2.29_3 (GND), U2.29_4 (GND), U2.29_5 (GND), U2.29_6 (GND), U2.29_7 (GND), U2.29_8 (GND), U2.29_9 (GND), U3.13 (GND), U4.1 (CTG), U4.4 (GND), U4.6 (QSTRT), U4.9 (EP)
GPIO8: R1.2, U2.10 (IO8)
I2C_PW: C1.1, C2.1, R1_PINH.2, R2-PINH.2, SENSOR2.2 (CSB), SENSOR2.6 (VDDIO), SENSOR2.8 (VDD), U2.17 (IO19)
INT_RTC: R1_PINH1.1, TP15.TP, U2.8 (IO0), U3.3 (SQW/!INT)
IO/BOOT: BOOT_BUTTON.3, BOOT_BUTTON.4, C6.1, R_BOOT.2, U2.15 (IO9)
IO/CHANGE: C10.1, CHANGE_BUTTON.3, CHANGE_BUTTON.4, R_CHANGE.2, U2.23 (IO15)
MISO: D12.1, J4.P7 (DAT0), R8.1, TP6.TP, U1.2 (DO(IO1)), U2.27 (IO2)
MOSI: D11.1, J1.14, J4.P3 (CMD), R7.1, TP7.TP, U1.5 (DI(IO0)), U2.7 (IO7)
unnamed: J2.B5, R2-USB.1
unnamed: C1_BAT1.1, D2.1 (CATHODE), IC4.1 (VIN), IC4.3 (CE), Q1.2 (S)
unnamed: MCP73831.1 (STAT), R1_BAT.1
unnamed: CHG_LED.C, R1_BAT.2
unnamed: J2.A5, R2-USB1.1
unnamed: MCP73831.5 (PROG), R2_BAT.2
unnamed: C4.1, D3.2 (A), D4.1 (K)
unnamed: C_DELAY.1, IC1.5 (CT)
unnamed: EPD_C2.1, J1.5
unnamed: EPD_C1.1, J1.4
unnamed: D7.1 (CATHODE), R_CAPACITOR.2
unnamed: EPD_C12.1, J1.24
unnamed: EPD_C10.1, J1.22
unnamed: EPD_C8.1, J1.20
unnamed: EPD_C7.1, J1.19
unnamed: EPD_C6.1, J1.18
PREVGH: D5.1 (K), EPD_C9.1, J1.21
PREVGL: D4.2 (A), EPD_C11.1, J1.23
RESE: J1.3, Q3.2 (S), R3.1
RESE': R2.2, R3.2, SJ1.2
RESET: C5.1, IC1.1 (VOUT), RESET_BUTTON.3, RESET_BUTTON.4, R_RESET.2, U2.3 (EN)
RTC_RST: U2.16 (IO18), U3.4 (!RST)
RX: TP2.TP, U2.24 (RXD0/GPIO17)
SCK: D10.1, J1.13, J4.P5 (CLK), R6.1, TP8.TP, U1.6 (CLK), U2.6 (IO6)
SCL: J3.4, R2-PINH.1, SENSOR2.4 (SCK), U2.20 (IO22), U3.16 (SCL), U4.7 (SCL)
SDA: J3.3, R1_PINH.1, SENSOR2.3 (SDI), U2.19 (IO21), U3.15 (SDA), U4.8 (SDA)
SRC: C4.2, D5.2 (A), L1.1, Q3.3 (D)
SS_SD: D8.1, J4.P2 (CD/DAT3), R10.1, U2.4 (IO4)
TX: TP1.TP, U2.25 (TXD0/GPIO16)
USB_D+: D1.1 (I/O1_1), U2.14 (IO13)
USB_D-: D1.3 (I/O2_1), U2.13 (IO12)
VBAT: C2_BAT.1, MCP73831.3 (VBAT), Q1.3 (D), TP3.TP, U4.2 (CELL), U4.3 (VDD)
VBUS: C1_BAT.1, C4_USB.1, C5_USB.1, CHG_LED.A, D1.5 (VBUS), D2.2 (ANODE), MCP73831.4 (VIN), PFMF.050.1.2, Q1.1 (G), R1_PWRUSB.2, TP14.TP
VRTC: C8.1, C10_SUPERCAP.2, R_CAPACITOR.1, U3.14 (VBAT)
VUSB: J2.A4, J2.A9, J2.B4, J2.B9, PFMF.050.1.1

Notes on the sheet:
USB C connector & ESD protection
LDO Voltage Regulator
SD Card
ESP32 C6
Display Type Selector
E-Paper Drive Circuit
Li-Po Battery Charging Controller
E-Paper Display Header
EPD Power
Environmental Sensor BME688
Voltage Supervisor + Reset & Boot / IO Button
Battery Charge Level
RTC Module DS3231SN
Test Pads
Qwiic / Stemma QT
SPI ESD Protection Lines
External NOR Flash 64MB
OpenBook Schematic
Dincă Tudor-Cristian

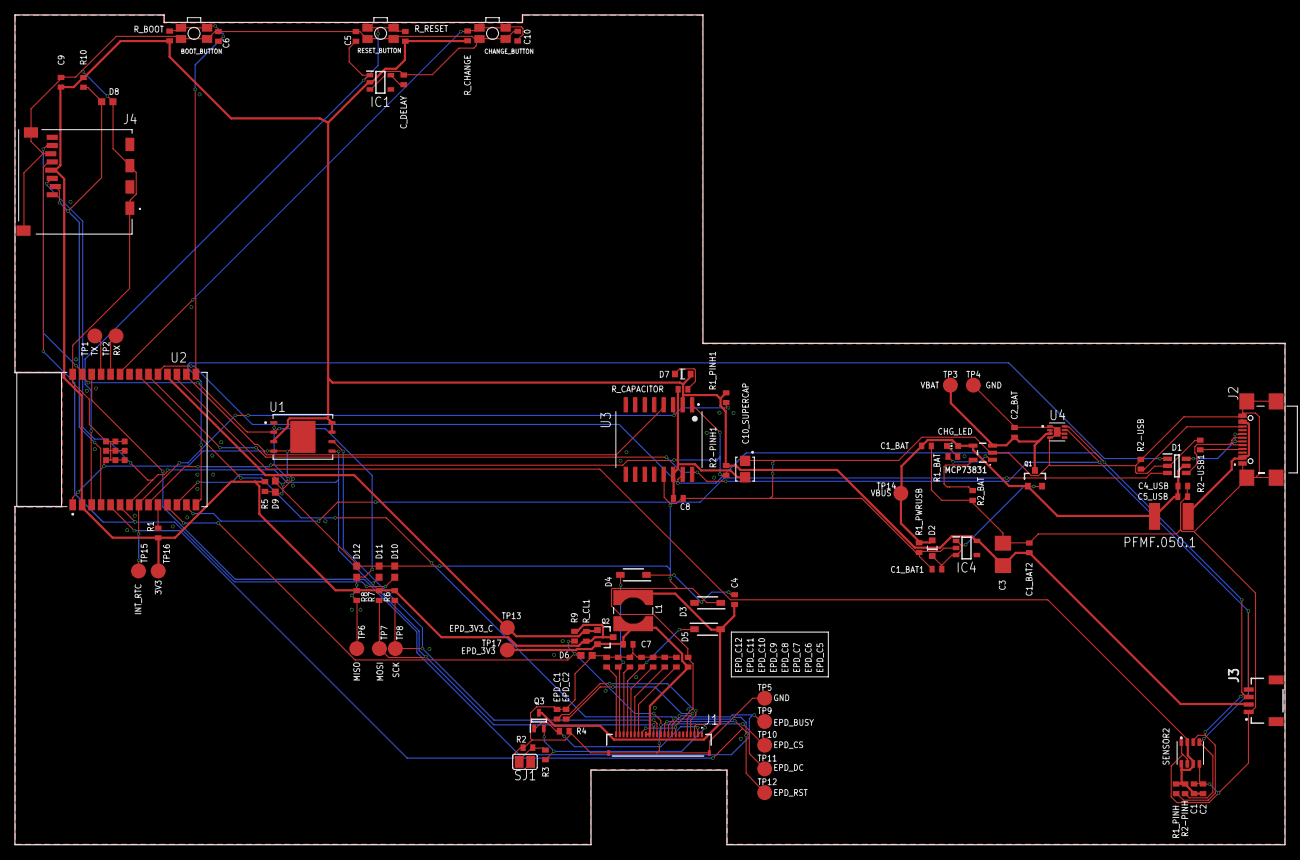
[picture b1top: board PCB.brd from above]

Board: 2 copper layers, 170.2 x 111.2 mm, 103 parts (0 on the bottom side), 55 nets.

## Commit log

2025-03-17 Created README.md
2025-04-04 Create LICENSE
2025-04-06 Added Hardware files
2025-04-06 Updated the names of the Hardware files
2025-04-06 Added the Manufacturing files
2025-04-06 Added the Mechanical files
2025-04-06 Added the Rendered Images
2025-04-06 Added README.md
2025-04-06 Added the Block Diagram to the README
2025-04-06 Rename BlockDiagram.png to blockdiagram.png
2025-04-13 Project update after the review
    Upon receiving a review, i updated my project to fix the signaled issues:
    - 90 degrees wires were eliminated
    - measurements around the board were added
    - the silkscreen has been cleared and enhanced to not intersect with the wires or the components
    - the ground plane is not covering the entire surface of both the TOP and BOTTOM layer
    - the board has now the correct 1mm width

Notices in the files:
parts and their libraries:
COPYRIGHT: Copyright (C) 2024 Ultra Librarian. All rights reserved.
